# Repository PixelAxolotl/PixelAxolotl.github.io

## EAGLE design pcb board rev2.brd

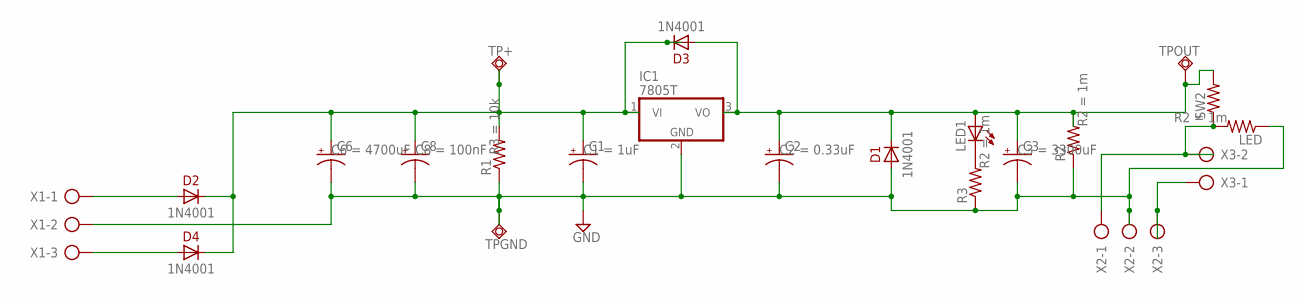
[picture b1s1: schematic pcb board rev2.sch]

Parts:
C1: CPOL-USE2,5-6E; E2,5-6E
C2: CPOL-USE2.5-6; E2,5-6
C3: CPOL-USE2.5-7; E2,5-7
C6: CPOL-USE7.5-16; E7,5-16
C8: CPOL-USE5-6; E5-6
D1, D2, D3, D4: 1N4001; DO41-10
IC1: 7805T; TO220H
LED: R-US_0207/10; 0207/10
LED1: LED5MM
R1, R2, R3: R-US_0207/10; 0207/10
SW2: R-US_0207/10; 0207/10
TP+: TPSQPAD1-13; P1-13
TPGND: TPSQPAD1-13; P1-13
TPOUT: TPSQPAD1-13; P1-13
X1, X2: AK500/3-H
X3: AK500/2-H

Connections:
12V: C2.+, C3.+, D1.C, D3.A, IC1.3 (VO), LED1.A, R2.2, SW2.2, TPOUT.TP
GND: C1.-, C2.-, C3.-, C6.-, C8.-, D1.A, IC1.2 (GND), LED.1, R1.1, R2.1, R3.1, TPGND.TP, X1.2, X2.2
unnamed: C1.+, C6.+, C8.+, D2.C, D3.C, D4.C, IC1.1 (VI), R1.2, TP+.TP
unnamed: LED.2, SW2.1, X2.1, X3.2
unnamed: LED1.K (C), R3.2
unnamed: D2.A, X1.1
unnamed: D4.A, X1.3
unnamed: X2.3, X3.1

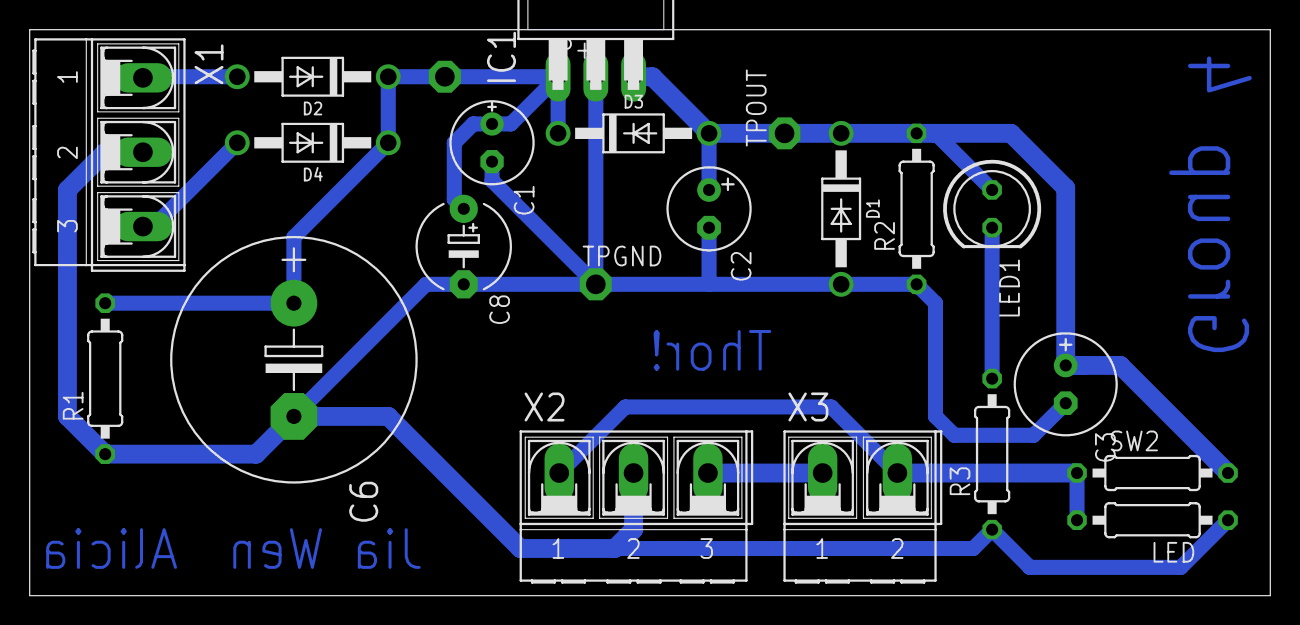
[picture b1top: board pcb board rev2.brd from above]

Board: 2 copper layers, 83.5 x 38.1 mm, 22 parts (0 on the bottom side), 8 nets.

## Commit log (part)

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2022-05-01 First ever thingie
    Well still in alpha
2022-05-01 finally added something call added a music player
    UwU
    SoS
    It was a pain
2022-05-01 mistake go brr
2022-05-01 Adding new thing try 2
2022-05-01 Updated file
2022-05-01 Update 2.0 cuz i am dum
2022-05-01 A bit of cleaning more soon
2022-05-04 some testing
2022-05-04 Edited
2022-06-04 Update v1
    Added history and orginised it
2022-06-04 updated typo
2022-06-06 Create CNAME
2022-06-06 um desktop dont work sos
    so idk :D
2022-06-06 TYPOOOOOO
2022-06-06 me dumdum
2022-06-06 dum dum again ...
2022-11-11 change . cat
    Meow~
2023-12-12 Update
    revamp the site
2026-01-14 Update LocationCheck_RandomQuotes.html
    Neaten code
